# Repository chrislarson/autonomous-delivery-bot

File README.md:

# megn540-project
Code and documentation for the mobile delivery robot

### Workflow:
Main branch is protected. To add code or documentation:
1. Clone the repo
2. Create a feature branch
3. Push to the feature branch
4. Open a pull request

### Using Typst:
1. VSCode Extension
    - There is a [TypstLSP extension](https://marketplace.visualstudio.com/items?itemName=nvarner.typst-lsp) for VSCode that can compile to pdf on save. It's listed in the recommended workspace extensions in `.vscode/extensions.json`.
2. CLI
    - The [Typst repo](https://github.com/typst/typst#installation) includes a section on platform-specific installation.

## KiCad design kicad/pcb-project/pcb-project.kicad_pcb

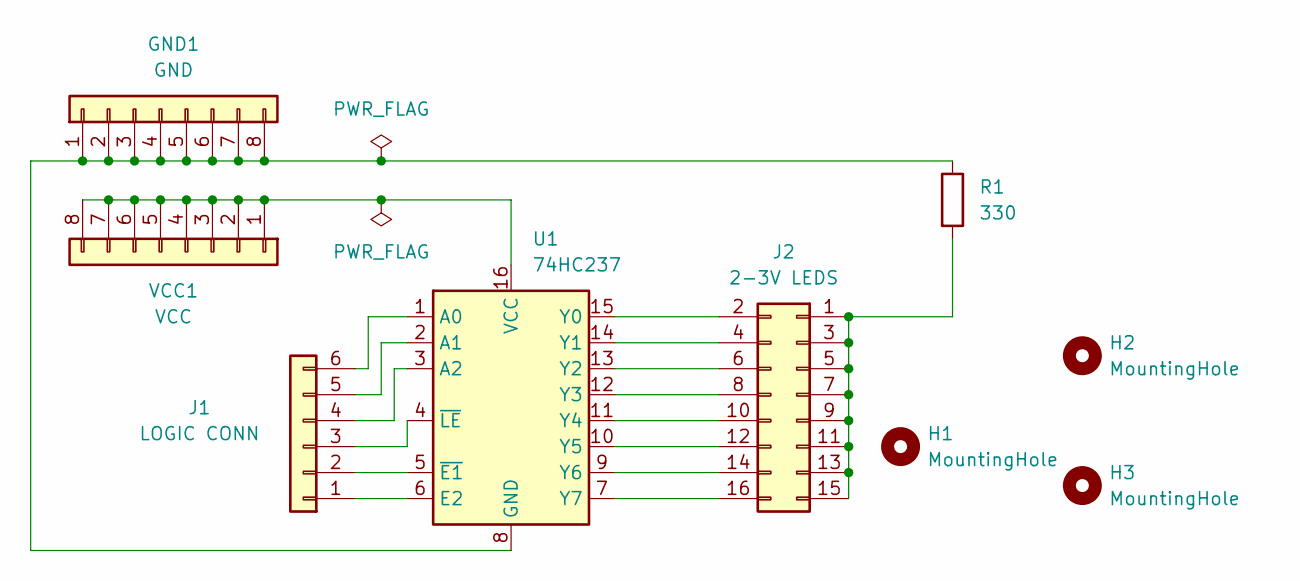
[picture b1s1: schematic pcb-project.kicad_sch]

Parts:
GND1: GND; PinSocket_1x08_P2.54mm_Vertical
H1, H2, H3: MountingHole; MountingHole_3.2mm_M3
J1: LOGIC CONN; PinSocket_1x06_P2.54mm_Vertical
J2: 2-3V LEDS; PinSocket_2x08_P2.54mm_Vertical
R1: 330; R_Axial_Power_L25.0mm_W9.0mm_P10.16mm_Vertical
U1: 74HC237; NS16
VCC1: VCC; PinSocket_1x08_P2.54mm_Vertical

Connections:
unnamed: GND1.1, GND1.2, GND1.3, GND1.4, GND1.5, GND1.6, GND1.7, GND1.8, R1.1, U1.8 (GND)
unnamed: J1.1, U1.6 (E2)
unnamed: J1.2, U1.5 (~E1)
unnamed: J1.3, U1.4 (~LE)
unnamed: J1.4, U1.3 (A2)
unnamed: J1.5, U1.2 (A1)
unnamed: J1.6, U1.1 (A0)
unnamed: J2.1, J2.3, J2.5, J2.7, J2.9, J2.11, J2.13, J2.15, R1.2
unnamed: J2.2, U1.15 (Y0)
unnamed: J2.4, U1.14 (Y1)
unnamed: J2.6, U1.13 (Y2)
unnamed: J2.8, U1.12 (Y3)
unnamed: J2.10, U1.11 (Y4)
unnamed: J2.12, U1.10 (Y5)
unnamed: J2.14, U1.9 (Y6)
unnamed: J2.16, U1.7 (Y7)
unnamed: U1.16 (VCC), VCC1.1, VCC1.2, VCC1.3, VCC1.4, VCC1.5, VCC1.6, VCC1.7, VCC1.8

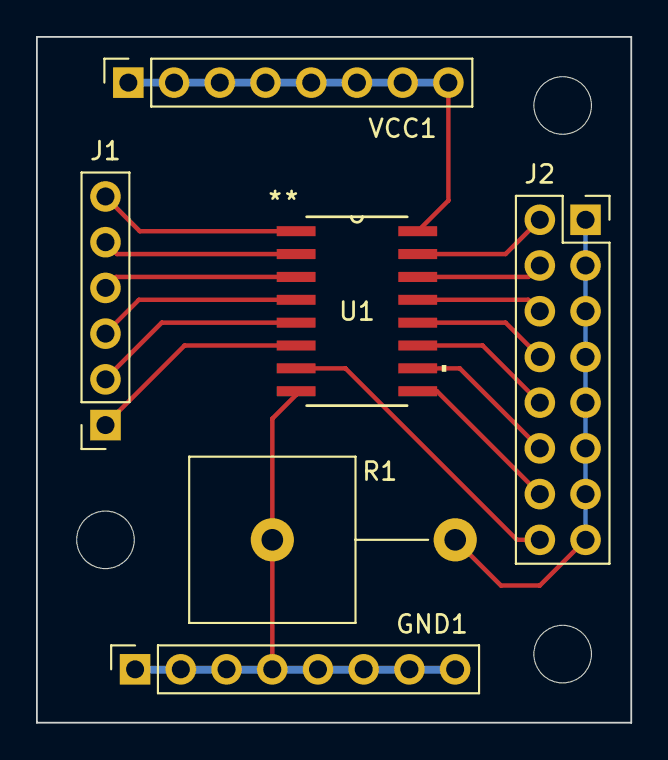
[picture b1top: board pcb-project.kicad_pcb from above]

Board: 2 copper layers, 33.0 x 38.1 mm, 9 parts (0 on the bottom side), 17 nets.

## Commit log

2024-01-25 Initialize repo and add outline for project proposal
2024-01-25 add workflow note
2024-01-25 add link to typst extension
2024-01-29 format a bit
2024-01-29 update plan
2024-01-29 Add first-pass proposal
2024-01-29 Update led indicators
2024-01-31 small edit
2024-01-31 Add some elaboration per rubric
2024-02-15 add dockerfile for ROS/CUDA development
2024-03-09 Designed schematic for pcb
2024-03-12 Add L4T devcontainer with Nvidia/Cuda, ROS2, l4t-pytorch, and Luxonis compiled on Jetson
2024-03-12 Convert schematic to board design
2024-03-12 Make annotations and wiring more readable
2024-03-13 Add python formatting plugin
2024-03-13 Add typst file and images for progress report. WIP
2024-03-14 Finish technical section of report. WIP on programmatic section.
2024-03-14 Add budget section
2024-03-14 Draft report complete.
2024-03-14 Finish progress report
2024-03-16 Add base odometry
2024-03-27 finish pcb
2024-04-03 wip - vo
2024-04-03 Working yoloV7 detection
2024-04-03 Added yolov7 deps
2024-04-12 move arduino code over from MEGN441-project
2024-04-12 Refactor LED code so id = 0 turns the LEDs off
2024-04-12 write serial commands for LED and PWM
2024-04-12 define msg lengths
2024-04-13 send raw encoder count data
2024-04-15 create python script to change leds
2024-04-15 setup leds
2024-04-16 fix leds
2024-04-16 have robot wait for enable command before enabling
2024-04-16 move LED code to another file
2024-04-16 move motor code to separate file
2024-04-16 move motor variables to above the functions responsible for updating them
2024-04-17 rewrite serial communication protocal
2024-04-17 invert motors
2024-04-17 comment out unecessary response from PWM command
2024-04-17 Add starter code for person detection & tracking
2024-04-17 Reduce moving average window & target lock frame count
2024-04-17 Starter code for Sys_ID request/response and waypoint
2024-04-18 remove unused command buffer
2024-04-18 make code compile
2024-04-18 explicity define no response to SYS_RESPONSE command sent to arduino
2024-04-19 Add basic spatial detector + trajectory generator
2024-04-19 Add requirements.txt
2024-04-19 Remove .venv from git
2024-04-19 define SysResponseCmd
2024-04-19 fix serialio to work for arguments of longer than one byte
2024-04-19 implement SysResponseCmd
2024-04-19 WIP system id script.
2024-04-19 Add write to png and csv
2024-04-19 double encoder resolution
2024-04-19 add error handling to serialio.py
2024-04-19 add serial commands for system id
2024-04-22 increase serial baud rate
2024-04-22 Added Disable Command to serial
2024-04-22 update baud in python files
2024-04-22 Add writing to csv
2024-04-22 fix minor syntax error
2024-04-22 testing disable command
2024-04-22 fix serial errors and disable robot on keyboard interrupt
2024-04-22 make sure recieved commands are the correct length on the arduino side
2024-04-22 75% of test forward
2024-04-22 add missing function call
2024-04-22 fix off by one error
2024-04-23 add new error command
2024-04-23 Added Error command and enum, started decode functionality
2024-04-23 change step to all fwd 80%, rev 20%, add wip chirp
2024-04-23 Implemented error decoding on unpacked struct
2024-04-23 add error reporting
2024-04-23 set error led for invalid cmd
2024-04-23 define prototypes for controller
2024-04-23 Add chirp traj
2024-04-23 Added functionality to controller definitions
2024-04-23 debugging drifty encoders
2024-04-23 lower chrip ending frequency
2024-04-24 Skid steer controller halfway implemented, fixed controller update
2024-04-25 Add sysid and controller matlab files
2024-04-25 Remove save tf
2024-04-25 record encoder profiling information
2024-04-25 Change to 2nd order system
2024-04-25 Add encoder profiling
2024-04-25 finish defining skid steer controller
2024-04-25 make skid steer update at specific period
2024-04-25 add basic implementation for waypoint command
2024-04-25 Refactor setpoint saturation for readability
2024-04-25 refactor skid_steer
2024-04-25 skid_steer debugging
2024-04-25 more progress
2024-04-26 Add base CLI
2024-04-26 outline lin and ang control modes
2024-04-26 add controller gains struct to manage mulitple gains profiles
2024-04-26 Added controller modes, update controller to take in mode
2024-04-26 finish implementing controller profiles
2024-04-26 Add basic drive command
2024-04-26 Run formatting
2024-04-26 switch to displacement control of motors instead of velocity control
2024-04-26 switch to displacement control on skid steer controllers
2024-04-26 Added displacement command to serial
2024-04-26 add trajectory start command
2024-04-26 Add disabling robot
2024-04-26 disable skid steer on displacement completion
2024-04-26 WIP CLI. Need to add targeting & waypoint generation.
2024-04-27 Implemented trajectory start cmd
2024-04-27 Implemented communication between trajectory start and displacement commands
2024-04-27 fixed trajectory command
2024-04-27 Add system ID data with full payload
2024-04-27 Add debug command
2024-04-27 Add debug message
2024-04-27 debug trajectory commands
2024-04-27 tune skid steer conversion ratios
2024-04-27 Add basic trajectory and delivery commands
2024-04-28 Fix displacement message typo
2024-04-28 Add ssh-compatible code
2024-04-28 Enable arduino before delivery
2024-04-28 clear recieve buffer if disabled
2024-04-28 lower max speed
2024-04-28 Disable interrupts during encoder count copy
2024-04-28 Add LED status to CLI (find targets)
2024-04-28 Add LED status conditions and switching based on state
2024-04-28 make closed loop control set led to ready when finished
2024-04-28 Add motor adjustments & trapezoid csv
2024-04-29 add wait functionality when robot sent 0 linear, 0 angular
2024-04-29 Add indicator for when robot is in turning mode
2024-04-29 Change skid steer zero to not fetch it's own encoder counts
2024-04-29 Change WaypointCmd to VelocityCmd and reimplement velocity control mode
2024-04-29 Added waypoint conversion to distance and angle
2024-04-29 Fixed typo
2024-04-29 Use angular velocity mode instead of linear velocity mode when the linear velocity is below 1mm/s
2024-04-29 Debugged waypoint conversion
2024-04-29 fix entering wait mode when angular displacement is zero
2024-04-29 fix motors stalling during wait mode
2024-04-29 ensure that skid_steer_update is not run when in wait mode
2024-04-29 add disp shorten:
2024-04-29 Change displacement to 70%
2024-04-29 Increase wait time to 5 seconds
2024-04-29 Add z coord update and lower ang disp threshold
2024-04-30 Clear traj buffer on disable
2024-04-30 Add lock photos
2024-04-30 Add data dir
2024-05-03 Branched and created outline for report
2024-05-03 fix error
2024-05-03 graph trapezoidal data
2024-05-03 WIP: Add person detector and motion planning pseudocode
2024-05-04 Began path planning, need to finish and add images
2024-05-04 submit PCB and serial communication writeups
2024-05-05 Add first pass description of person detector
2024-05-05 Add problem, design, sensor, and actuator from progress report
2024-05-05 Compiled individual contributions, added sections, and images. 90% done
2024-05-05 Made changes to the conclusion
2024-05-05 Add works cited
2024-05-06 Finalize report
